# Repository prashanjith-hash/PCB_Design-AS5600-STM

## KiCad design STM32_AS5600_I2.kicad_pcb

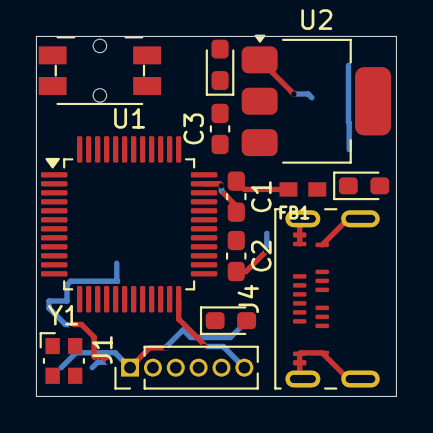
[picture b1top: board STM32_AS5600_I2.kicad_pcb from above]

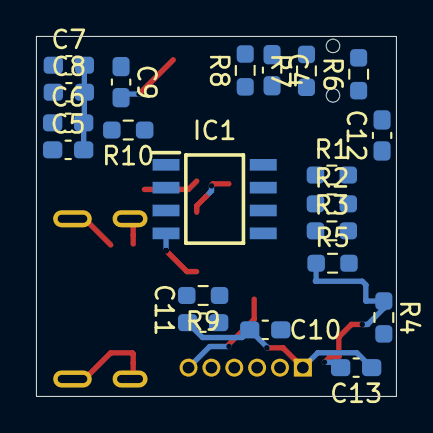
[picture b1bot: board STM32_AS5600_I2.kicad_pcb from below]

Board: 2 copper layers, 20.0 x 20.0 mm, 34 parts (21 on the bottom side), 24 nets.

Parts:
C1, C2, C3, C4, C9: 100n; C_0603_1608Metric_Pad1.08x0.95mm_HandSolder
C5: 10u; C_0603_1608Metric_Pad1.08x0.95mm_HandSolder
C6: 10n; C_0603_1608Metric_Pad1.08x0.95mm_HandSolder
C7, C8: 1u; C_0603_1608Metric_Pad1.08x0.95mm_HandSolder
C10, C11: 30p; C_0603_1608Metric_Pad1.08x0.95mm_HandSolder
C12, C13: 22u; C_0603_1608Metric_Pad1.08x0.95mm_HandSolder
D1, D2, D3: LED; LED_0603_1608Metric_Pad1.05x0.95mm_HandSolder
FB1: 120R; FB_LI0603G121R-10
IC1: AS5600-ASOT; SOIC127P600X175-8N
J1: Conn_01x06_Pin; PinHeader_1x06_P1.27mm_Vertical
J4: USB_C_Receptacle_USB2.0_16P; USB_C_Receptacle_Amphenol_124019772112A
R1, R3, R6: 10k; R_0603_1608Metric_Pad0.98x0.95mm_HandSolder
R2: 1k5; R_0603_1608Metric_Pad0.98x0.95mm_HandSolder
R4: 4K7; R_0603_1608Metric_Pad0.98x0.95mm_HandSolder
R5: 4k7; R_0603_1608Metric_Pad0.98x0.95mm_HandSolder
R7, R8: 5K1; R_0603_1608Metric_Pad0.98x0.95mm_HandSolder
R9: 220; R_0603_1608Metric_Pad0.98x0.95mm_HandSolder
R10: 1K; R_0603_1608Metric_Pad0.98x0.95mm_HandSolder
SW1: SW_SPDT; Panasonic_EVQPUL_EVQPUC
U1: STM32F103C8T6; LQFP-48_7x7mm_P0.5mm
U2: AMS1117-3.3; SOT-223-3_TabPin2
Y1: 8MHz; Crystal_SMD_Abracon_ABM10-4Pin_2.5x2.0mm

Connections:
+3.3V: C1.1, C2.1, C3.1, C4.1, C5.1, C8.1, C13.2, D1.2 (A), FB1.2, IC1.1 (VDD5V), IC1.2 (VDD3V3), J1.6, R3.2, R4.1, R5.1, R6.2, U1.1 (VBAT), U1.24 (VDD), U1.36 (VDD), U1.48 (VDD), U2.2 (VO)
+3.3VA: C6.1, C7.1, FB1.1, U1.9 (VDDA)
/BOOT: R1.2, U1.44 (BOOT0)
/DIR: IC1.8 (DIR), U1.39 (PB3)
/HSE_IN: C10.1, U1.5 (PD0), Y1.1
/HSE_OUT: C11.1, U1.6 (PD1), Y1.2
/I2C_SCL: IC1.7 (SCL), R4.2, U1.21 (PB10)
/I2C_SDA: IC1.6 (SDA), R5.2, U1.22 (PB11)
/NRST: C9.1, U1.7 (NRST)
/OUT: IC1.3 (OUT), U1.40 (PB4)
/PGO: IC1.5 (PGO), U1.20 (PB2)
/SWCLK: J1.5, U1.34 (PA13)
/SWDIO: J1.4, U1.37 (PA14)
CC1: J4.A5 (CC1), R7.2
CC2: J4.B5 (CC2), R8.2
GND: C1.2, C2.2, C3.2, C4.2, C5.2, C6.2, C7.2, C8.2, C9.2, C10.2, C11.2, C12.2, C13.1, D2.1 (K), D3.1 (K), IC1.4 (GND), J1.1, J4.A1 (GND), J4.A12 (GND), J4.B1 (GND), J4.B12 (GND), J4.S1 (SHIELD), R2.2, R7.1, R8.1, U1.8 (VSSA), U1.23 (VSS), U1.35 (VSS), U1.47 (VSS), U2.1 (GND)
unnamed: D1.1 (K), R2.1
unnamed: D2.2 (A), R9.1
unnamed: D3.2 (A), R10.2
unnamed: R1.1, SW1.2 (B)
unnamed: R9.2, U1.2 (PC13)
USB_D+: J4.A6 (D+), J4.B6 (D+), R3.1, R6.1, U1.33 (PA12)
USB_D-: J4.A7 (D-), J4.B7 (D-), U1.32 (PA11)
V_BUS: C12.1, J4.A4 (VBUS), J4.A9 (VBUS), J4.B4 (VBUS), J4.B9 (VBUS), R10.1, U2.3 (VI)
